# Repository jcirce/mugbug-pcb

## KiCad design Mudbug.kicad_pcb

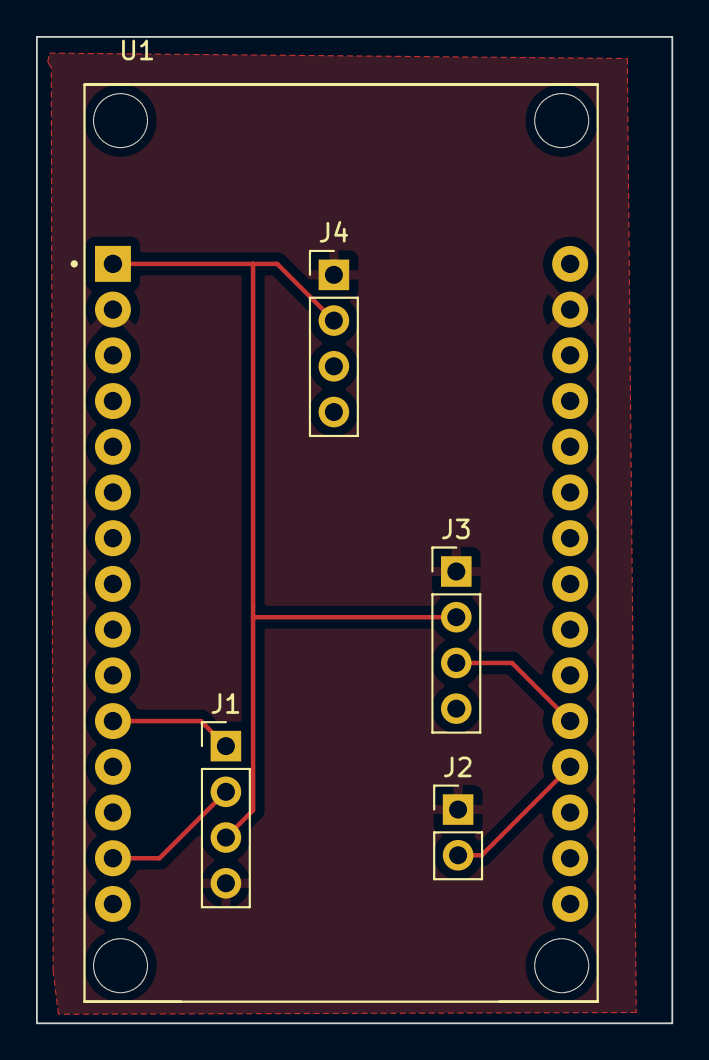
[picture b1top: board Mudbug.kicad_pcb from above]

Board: 2 copper layers, 35.3 x 54.8 mm, 5 parts (0 on the bottom side), 6 nets.

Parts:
J1: Teeny sensor with 4; PinHeader_1x04_P2.54mm_Vertical
J2: Teeny sensor with 2; PinHeader_1x02_P2.54mm_Vertical
J3: Gas Sensor; PinHeader_1x04_P2.54mm_Vertical
J4: Other Gas Sensor; PinHeader_1x04_P2.54mm_Vertical
U1: ESP32-DEVKIT-V1; MODULE_ESP32_DEVKIT_V1

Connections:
/+3V3: J1.3, J3.2, J4.2, U1.1 (3V3)
/GND: J1.4, J2.1, J3.1, J4.1, U1.2 (GND), U1.29 (GND)
/S1: J1.1, U1.11 (D21)
/S2: J1.2, U1.14 (D22)
/S3: J2.2, U1.19 (D34)
/S4: J3.3, U1.20 (D35)

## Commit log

2023-02-05 setting up repo
2023-02-05 setup kicad
2023-02-05 adding generic footprint libs
2023-02-05 built schematic with 4 sensors
2023-02-05 added traces
